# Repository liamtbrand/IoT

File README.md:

# IoT
This project aims to create a simple control system for home lighting.
Users can control the lighting in their house from their phones,
and setup triggers with geofencing to turn on and off lights based on their location.

-
#### Hub:
The purpose of the hub is to talk to and manage local nodes.
The hub talks to the cloud and relays changes to/from the nodes.
Settings for the hub are stored locally, but can be managed from the cloud.

-
#### Nodes:
The nodes are designed to be linked to a hub which is linked to the cloud.

Nodes have two modes, setup and node mode.
When in setup mode, the hub acts as an AP,
where it will serve up a web page that allows a few basic settings to be changed.
These settings are for the accesspoint this node connects to, and for the hub ip.

Once the node has successfully established a connection with the hub,
it then talks to the hub, and verifies using the cloud.

#### Components:
* Node Hardware
* Node Software
* Hub Hardware
* Hub Software
* "Cloud" Software (Web App)

#### TODO List:
* Node
  * Modular hardware design
* Hub
  * 
* "Cloud" (Web App)
  *

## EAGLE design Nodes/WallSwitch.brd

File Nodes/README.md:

# Schematics

The files .sch are schematics for the design of the wall switch.

The upper left part of the design is the switch input control.
This pulls PinX LOW when the switch is closed, and HIGH when open.
WallSwitch.h contains the code to get this input.

The lower right part of the design is the controlled switch.
This will connect the mains power supply when the pin is pulled LOW,
and will disconnect the power when the pin is pulled HIGH.
PowerSwitch.h contains the code to control this switch.

On powerup the esp should be checking to see the last known status of the switch from the server, and restoring this.

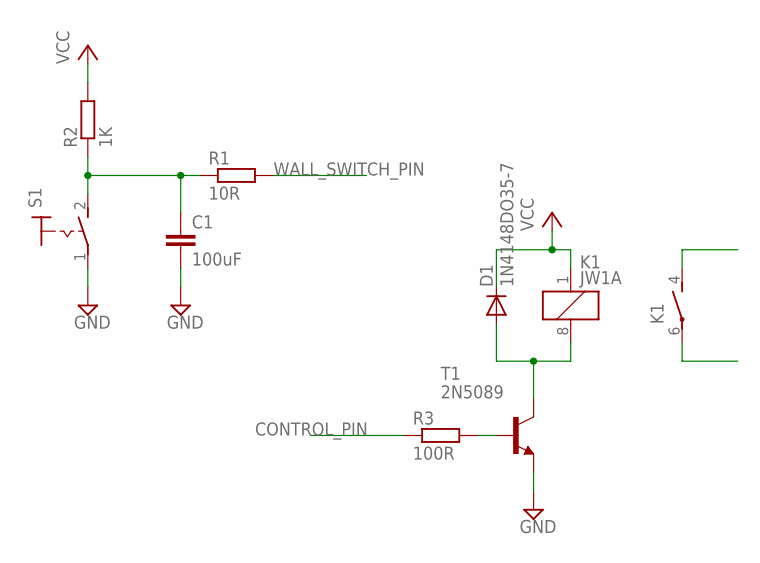
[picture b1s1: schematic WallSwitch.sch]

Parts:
C1: 100uF; C025-024X044
D1: 1N4148DO35-7; DO35-7
K1: JW1A
R1: 10R; 0204/5
R2: 1K; 0204/5
R3: 100R; 0204/5
S1: MS243
T1: 2N5089; TO92

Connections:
CONTROL_PIN: R3.1
GND: S1.1, T1.3 (E)
unnamed: C1.1, R1.1, R2.1, S1.2 (S)
unnamed: R3.2, T1.2 (B)
unnamed: D1.A, K1.8 (2), T1.1 (C)
VCC: D1.C, K1.1, R2.2
WALL_SWITCH_PIN: R1.2

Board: 2 copper layers, 8 parts (0 on the bottom side), 5 nets, no tracks yet.

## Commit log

2017-02-17 Begin Works
2017-02-17 Create wifi connection class
2017-02-17 Fix code errors
2017-02-18 Reworked connection config
2017-02-18 Fixes
2017-02-18 Refactoring to classes
2017-02-18 Reworking
2017-02-20 Create hub service
2017-02-20 Hub and node talk (echo hub)
2017-02-20 Updates
    LED should be lit up when connection success.
2017-03-13 Add wall switch schematics
2017-03-13 Refactoring
2017-03-13 Add info sheets
2017-03-19 Add pdf schematics
    For quick viewing of schematics
2017-04-14 Trying to get led to work
2017-04-14 Schematic changes
2017-04-14 Makes webpage setup work
2017-04-15 Development changes
2017-04-16 Working on modular design
2017-04-16 Setup UI
2017-04-17 Many additions to website display
2017-04-17 Improvements to profile page in the web interface
2017-04-17 Updates small changes
2017-04-18 Update README.md
    Added components and todo list... need to finish these still.
2017-04-18 Working to add testing setup
2017-04-19 Makes light controllable from hub.py
2017-04-20 Debounced wall switch pin
2017-04-21 Simple switch ability
2017-04-22 Working on stuff
2017-04-22 Hub software rewritten for java
2017-04-22 Web + Hub + Node model
2017-04-23 Adds JSON parsing for config
2017-04-23 Updates for OTA
2017-04-23 OTA Updates now work
2017-04-23 Removes some old code that's not used
2017-04-23 Adds keep alive packets to node
2017-04-23 Reinstates semantic ui in the web interface
2017-04-24 Ignore node modules
2017-04-24 Ignore node_modules directory
2017-04-24 Removes node_modules from app directory
2017-04-24 Removes semantic ui dependency files from repo
2017-04-24 Update dependency installer
2017-04-25 Writing the cloud software
2017-04-27 Adds NodeID generation class
2017-04-27 Adds build and run scripts for cloud
2017-04-27 Initial build of cloud (testing)
2017-04-27 Cloud recompiled for java7
2017-04-27 Recompiles cloud again
2017-04-30 Small changes
2017-04-30 Networking specification overview
    (test)
2017-04-30 Jar for testing cloud
2017-04-30 Fixes code error in cloud
2017-04-30 Implements Cloud <-> Hub model
2017-04-30 Adds debug connection to iPhone
2017-04-30 Fixes chewing through cpu on ec2 vm
2017-05-14 Adds RDS config file
2017-05-14 Adds Driver for MySQL
2017-05-14 Adds database interaction
2017-05-21 Minor changes to hub connection
